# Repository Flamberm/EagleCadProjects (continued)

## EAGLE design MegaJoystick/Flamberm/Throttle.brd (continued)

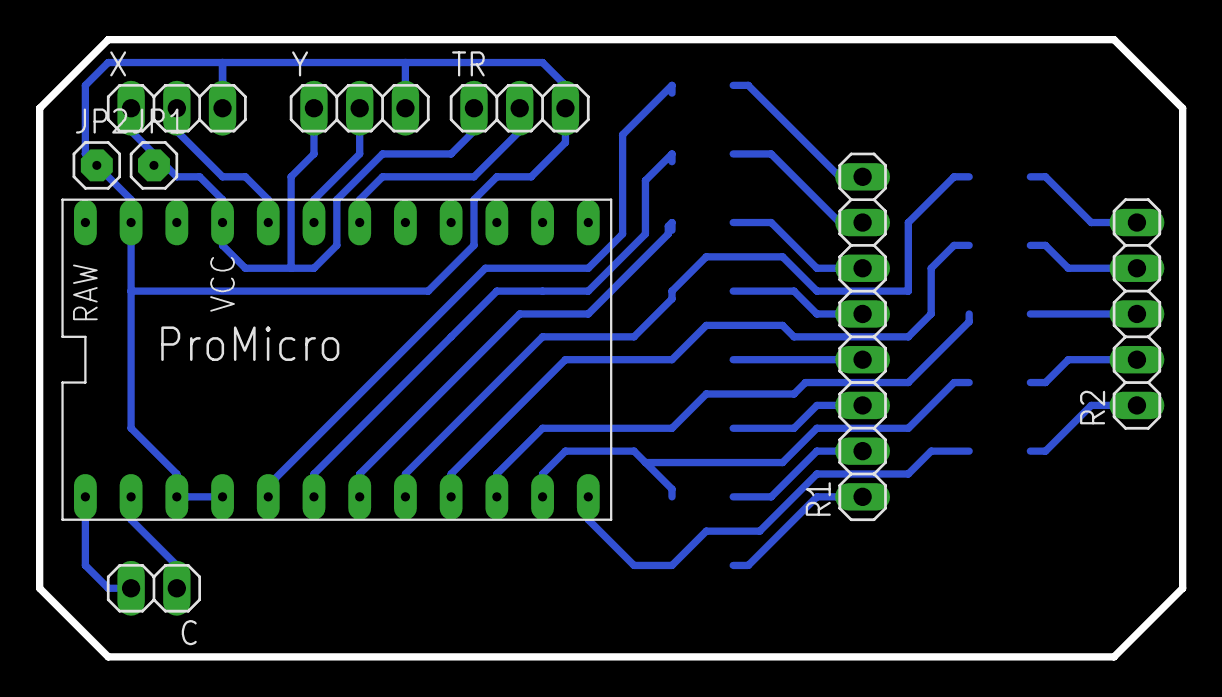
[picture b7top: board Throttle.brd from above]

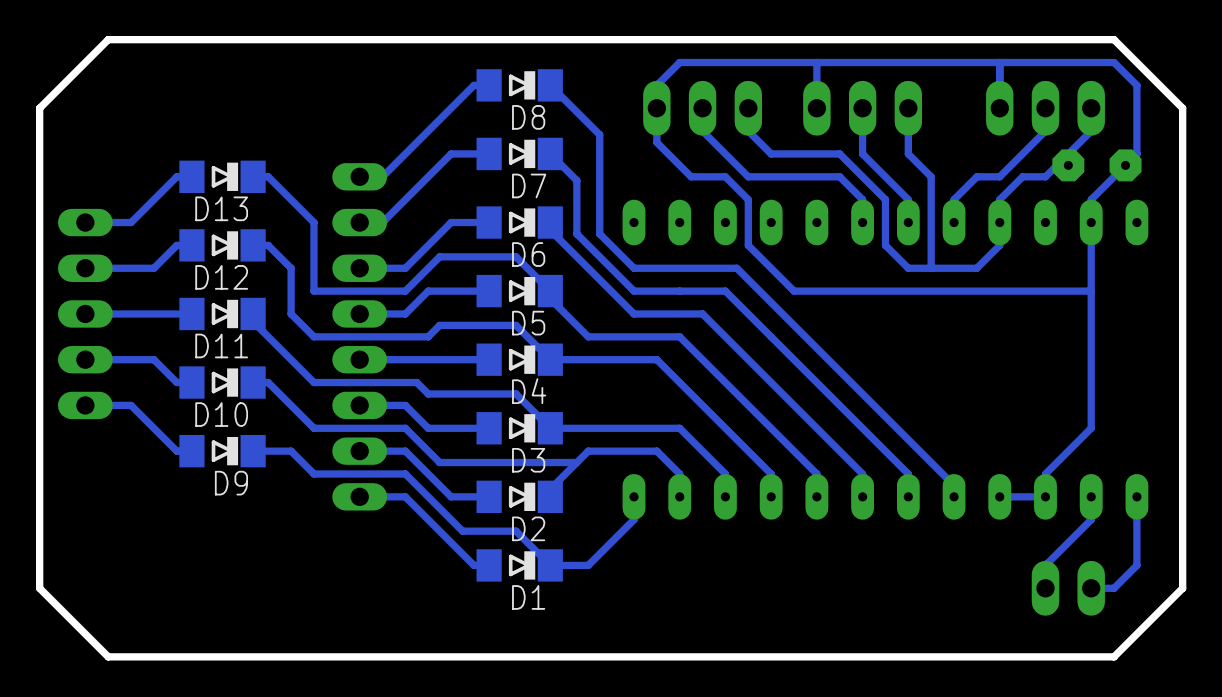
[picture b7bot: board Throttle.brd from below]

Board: 2 copper layers, 63.5 x 34.3 mm, 22 parts (13 on the bottom side), 28 nets.
